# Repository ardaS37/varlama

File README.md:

# Varlama — Card and Phone Attendance System

Varlama is an experimental attendance system designed for boarding houses, dormitories, hostels, and other managed facilities. It combines an ESP32 reader with an optional Android phone-card application so that authorized residents can record attendance without sharing personal identity data with the reader.

## Part 1 — ESP32 card reader and attendance panel

The ESP32 firmware reads RFID/MIFARE cards through an RC522 module, stores authorized credentials and attendance records on an SD card, and shows the latest result on an I2C LCD. A local web panel is served by the device for registering cards, managing residents, configuring Wi-Fi, and exporting attendance data as CSV.

The firmware can also operate as a Wi-Fi access point when an external network is unavailable. Attendance records are designed around a daily check-in model, preventing duplicate entries for the same person on the same day.

### Main hardware

- ESP32 development board
- RC522 RFID reader
- SD card module
- I2C LCD
- Optional Android phone with NFC host-card emulation

The pin mapping and PlatformIO dependencies are documented in `platformio.ini` and the source comments. Before deployment, set a strong local access-point password in `src/main.cpp` and configure the device through the web panel.

## Part 2 — Android phone-card application

The `android-phone-card/` module turns an NFC-capable Android phone into a reusable attendance card. The app stores a provisioned credential locally and exposes it through Android Host Card Emulation (HCE). An administrator can open the phone-provisioning mode on the ESP32, write a one-time credential to the phone, and then use the phone at the reader like a physical card.

The phone app is intentionally small: it provides a provisioning screen, secure local storage for the assigned credential, and an HCE service that responds only to the Yoklama application protocol. It does not contain a server account or a hard-coded student list.

### Android setup

1. Open `android-phone-card/` in Android Studio.
2. Copy `master-key.properties.example` to `master-key.properties` only for local signing configuration.
3. Build and install the debug APK on an NFC-capable Android device.
4. Arm provisioning from the app, then use the ESP32 web panel to assign the phone.

Build output and signing files are intentionally ignored and are not part of this repository.

## Data and privacy notes

Use institution-specific identifiers instead of national ID numbers. Keep the ESP32 panel on a trusted local network, change all default credentials, and protect exported CSV files. This project is a prototype and has not been audited for production security or attendance-law compliance.

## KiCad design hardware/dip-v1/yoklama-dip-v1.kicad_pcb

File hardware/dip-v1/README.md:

# Yoklama — doğrudan lehimlenen modüller için DIP/THT kart, v1

Bu sürüm, hazır ESP32 geliştirme kartı ve modüllerin erkek pinlerini ana PCB'nin deliklerine doğrudan lehimlemek içindir. Ana kart üzerinde SMD montaj yoktur; modüllerin kendi üzerlerindeki SMD parçalar hazır modülün parçasıdır. Soket gerekmez.

**Durum: elektriksel ve PCB kural kontrolleri tamamlanmış prototip tasarım. Fiziksel montaj, USB akım bütçesi ve çalışır cihaz testi yapılmadı.** Gerberlerin bulunması bu testlerin yapıldığı anlamına gelmez.

## Dosyalar

- `yoklama-dip-v1.kicad_pro`: KiCad 10 projesi.
- `yoklama-dip-v1.kicad_sch`: bağlantı şeması; modül ve destek bileşenleri pin adlarıyla gösterilir.
- `yoklama-dip-v1.kicad_pcb`: yolları çizilmiş iki katmanlı PCB.
- `Yoklama.pretty`, `Yoklama.kicad_sym`, `fp-lib-table`, `sym-lib-table`: proje içi kütüphaneler; taşınırken birlikte tutulmalı.
- `BOM.csv`: parça listesi; `pinout.csv`: firmware ile eşleştirilmiş bağlantılar.
- `exports/assembly.svg`: üst yüzün gerçek KiCad montaj/baskı çizimi.
- `exports/board.svg`: iki bakır katman ve üst baskı.
- `exports/yoklama-dip-v1.svg`: şema önizlemesi.
- `gerbers/`: 7 Gerber katmanı, PTH ve NPTH delik dosyaları ve Gerber iş dosyası.
- `reports/erc.rpt`, `reports/drc.rpt`: son KiCad kontrolleri.
- `reports/verification.json`: kod, şema ve PCB bağlantılarının karşılaştırması.

## Kart ve besleme

| Özellik | Değer |
|---|---|
| Ana PCB | 152,4 × 127 mm, dikdörtgen |
| Katman | 2 bakır katman |
| Önerilen malzeme | FR-4, 1,6 mm, 1 oz bakır |
| Sinyal yolları | 0,30 mm |
| Güç/toprak yolları | 0,80 mm, iki yüzde GND dolgu |
| Minimum açıklık | 0,25 mm |
| Modül pin delikleri | 1,00 mm bitmiş PTH; 1,80 mm pad |
| Modül pin adımı | 2,54 mm |
| ESP32 sıra aralığı | 25,40 mm, 2 × 19 pin |
| Montaj delikleri | 4 × 3,20 mm NPTH, M3 |
| Besleme | Yalnızca ESP32 geliştirme kartının USB girişi |

USB'den gelen 5 V, geliştirme kartının 5V pininden SD modülüne, LCD'ye ve buzzer devresine dağıtılır. RC522 ve I²C'nin ESP tarafı geliştirme kartının 3V3 çıkışını kullanır. Ana kartta ayrı adaptör girişi yoktur. USB kaynağının ve geliştirme kartının 5 V yolunun toplam yüke uygunluğu ilk cihazda ölçülmelidir; bilgisayar USB portundan sınırsız akım varsayılmadı.

## Modül yerleşimi ve yön

Tüm yönler **üstten, modüllerin takıldığı yüzden görünüş** içindir. Alt yüz bakırını elle aynalamayın; üretim dosyaları doğru katman yönleriyle dışa aktarıldı.

- **U1:** ESP32-DevKitC V4 / WROOM, 38 pin, anten üstte ve USB aşağıda. Solda üst pin 3V3, sol alt pin 5V; sağ üst pin GND. `SD0/1/2/3`, `CMD`, `CLK` gibi flash pinleri bağlanmadı. WROVER, S3 veya 30 pinli kart için uygun değildir.
- **J1:** 8 pinli RC522, soldan sağa `SDA/SS, SCK, MOSI, MISO, IRQ, GND, RST, 3V3`. IRQ boş bırakıldı. Modül gövdesi pin sırasının üstüne doğru uzanır. Yer ayrılan zarf yaklaşık 40 × 60 mm; modül montaj delikleri için tahminle delik açılmadı.
- **J2:** Kullanıcının fotoğrafındaki 42 × 24 mm, regülatör ve seviye tamponu taşıyan microSD modülü. Üstten alta `GND, VCC, MISO, MOSI, SCK, CS`; gövde pinlerin sağına uzanır. VCC=5 V. Bu bağlantı çıplak microSD soketi veya regülatörsüz 3,3 V kart için değildir.
- **J3:** Klasik PCF8574 I²C LCD, soldan sağa `GND, VCC, SDA, SCL`. 4 pin doğrudan lehim bağlantısıdır. LCD kenarda dik montaj için düşünülmüştür; mevcut açılı pinleri hizalanmalıdır. LCD'nin ekran gövdesi, vida aralıkları ve kutusu bu revizyonda ölçülendirilmedi; 4 pin bağlantısı LCD için tek başına mekanik taşıyıcı sayılmamalıdır.

Üretimden önce `assembly.svg` gerçek boyutta (%100, sayfaya sığdır kapalı) basılıp modüllerin pinleriyle karşılaştırılmalıdır. Kullanıcının kabul ettiği standart ESP32 ayak izi esas alındı; fiziksel kart ölçülmedi. Sağ açılı pinleri olan modüller için pin yönü fiziksel montaj sırasında dikkate alınmalıdır.

ESP32 ve RC522 antenlerinin altında her iki bakır katmanda yol, via, pad ve dolgu yasak alanları bulunur. Bu bölgelere metal bağlantı elemanı eklenmemelidir.

## Firmware bağlantıları

| Modül | Sinyal | GPIO |
|---|---|---:|
| RC522 | SDA/SS | 5 |
| RC522 | SCK | 18 |
| RC522 | MISO | 19 |
| RC522 | MOSI | 23 |
| RC522 | RST | 27 |
| SD | CS | 33 |
| SD | SCK | 14 |
| SD | MISO | 25 |
| SD | MOSI | 26 |
| LCD | SDA, 3,3 V tarafı | 21 |
| LCD | SCL, 3,3 V tarafı | 22 |
| Hazır LED | Direnç üzerinden | 4 |
| Başarılı işlem LED | Direnç üzerinden | 16 |
| Hata LED | Direnç üzerinden | 17 |
| Ağ LED | Direnç üzerinden | 13 |
| Buzzer | Sürücü üzerinden | 32 |

Kod değiştirilmedi. `src/main.cpp` içindeki sabitler esas alındı. RC522 için `SPI.begin()` / `esp32dev` varsayılan VSPI pinleri kullanılır. SD ayrı HSPI pinlerindedir. Eski kök README'deki SD pinlerini kullanmayın. Firmware LCD'yi `16×2`, I²C adresini `0x3F` olarak başlatır; `0x27` adresli bir LCD'de adresi değiştirmek gerekir.

## Destek parçaları ve polarite

- R1–R4: 1 kΩ, 1/4 W; D1–D4: 5 mm LED, 2,54 mm bacak aralığı. LED pad 1=K/katot, pad 2=A/anot. Kare pad katottur. Mavi LED'in parlaklığı ileri gerilimine bağlı olarak düşük olabilir.
- Q1, Q2: **2N7000**, TO-92; pad 1=source, 2=gate, 3=drain. Bacaklar 2,54 mm aralığa açılır. Gate 3V3'e, source ESP32 tarafına, drain LCD'nin 5 V tarafına bağlıdır. R5–R8=4,7 kΩ çekme dirençleri. LCD sırt kartındaki çekme dirençleri 5 V tarafında kalır. Bu dönüştürücü prototipte 100 kHz I²C ile test edilmelidir.
- Q3: **BC337-40**, TO-92; pad 1=collector, 2=base, 3=emitter. R9=1 kΩ, R10=100 kΩ.
- BZ1: **pasif piezo**, 5 V, en fazla 12 mm gövde, 7,62 mm bacak aralığı, en fazla 20 mA. Pad 1 pozitif. Aktif buzzerla firmware'in farklı frekanslı `tone()` sesleri elde edilmez. R11=10 kΩ deşarj direnci; D5=1N4148, pad 1 katot/bant, pad 2 anot.
- C1=100 µF/10 V, C4=10 µF/10 V; 2,54 mm bacak aralığı ve en fazla 5 mm gövde. Kare pad 1 pozitif, pad 2 GND. C2/C3/C5=100 nF seramik, 2,54 mm bacak aralığı, polaritesiz.
- R12/R13=10 kΩ; RC522 ve SD seçme hatlarını açılışta 3V3'e çeker.

Destek parçaları için belirtilen kılıf, bacak sırası ve gövde ölçüsü BOM'un parçasıdır; aynı isimli farklı üretici/kılıf otomatik olarak eşdeğer kabul edilmemelidir.

## Kontrol kapsamı

KiCad ERC, bakır aralıkları, bağlantısız padler ve şema-PCB eşleşmesi kontrol edildi. GPIO eşlemesi ayrıca mevcut firmware sabitleriyle karşılaştırıldı. RF performansı, SPI sinyal bütünlüğü, SD yazma sırasında besleme düşümü, LCD'nin gerçek adresi ve mekanik montaj ancak ilk fiziksel prototiple doğrulanabilir. Bu revizyon için üretim siparişi verilmedi.

## Yeniden üretme

KiCad 10 ile gelen Python'da `pcbnew` ve `numpy` kullanılır. `build_design.py` PCB'yi sıfırdan oluşturur ve elle yapılan değişiklikleri üzerine yazar; elle düzenlemeden önce kopya alın.

1. `build_design.py` çalıştırılır.
2. KiCad CLI ile şema netlisti `reports/schematic.net` dosyasına aktarılır.
3. `route_board.py`, sonra `finish_board.py` çalıştırılır.
4. KiCad CLI `pcb drc --refill-zones --save-board --schematic-parity` ve `sch erc` çalıştırılır.
5. `verify_design.py` çalıştırılır; dışa aktarımlar son PCB'den yenilenir.

## Referanslar

- [Espressif DevKitC V4 ölçü çizimi](https://dl.espressif.com/dl/schematics/esp32_devkitc_v4_dimensions.pdf)
- [Espressif DevKitC V4 şeması](https://dl.espressif.com/dl/schematics/esp32_devkitc_v4-sch.pdf)
- [Espressif DevKitC pinleri ve besleme seçenekleri](https://docs.espressif.com/projects/esp-idf/en/release-v4.4/esp32/hw-reference/esp32/get-started-devkitc.html)
- [NXP PCF8574 veri sayfası](https://www.nxp.com/docs/en/data-sheet/PCF8574_PCF8574A.pdf)
- [onsemi 2N7000 veri sayfası](https://www.onsemi.com/pdf/datasheet/nds7002a-d.pdf)
- [onsemi BC337 veri sayfası](https://www.onsemi.com/pdf/datasheet/bc337-fsc-d.pdf)
- SD modülü: kullanıcının paylaştığı pin etiketleri ve 42 × 24 mm boyut görseli.

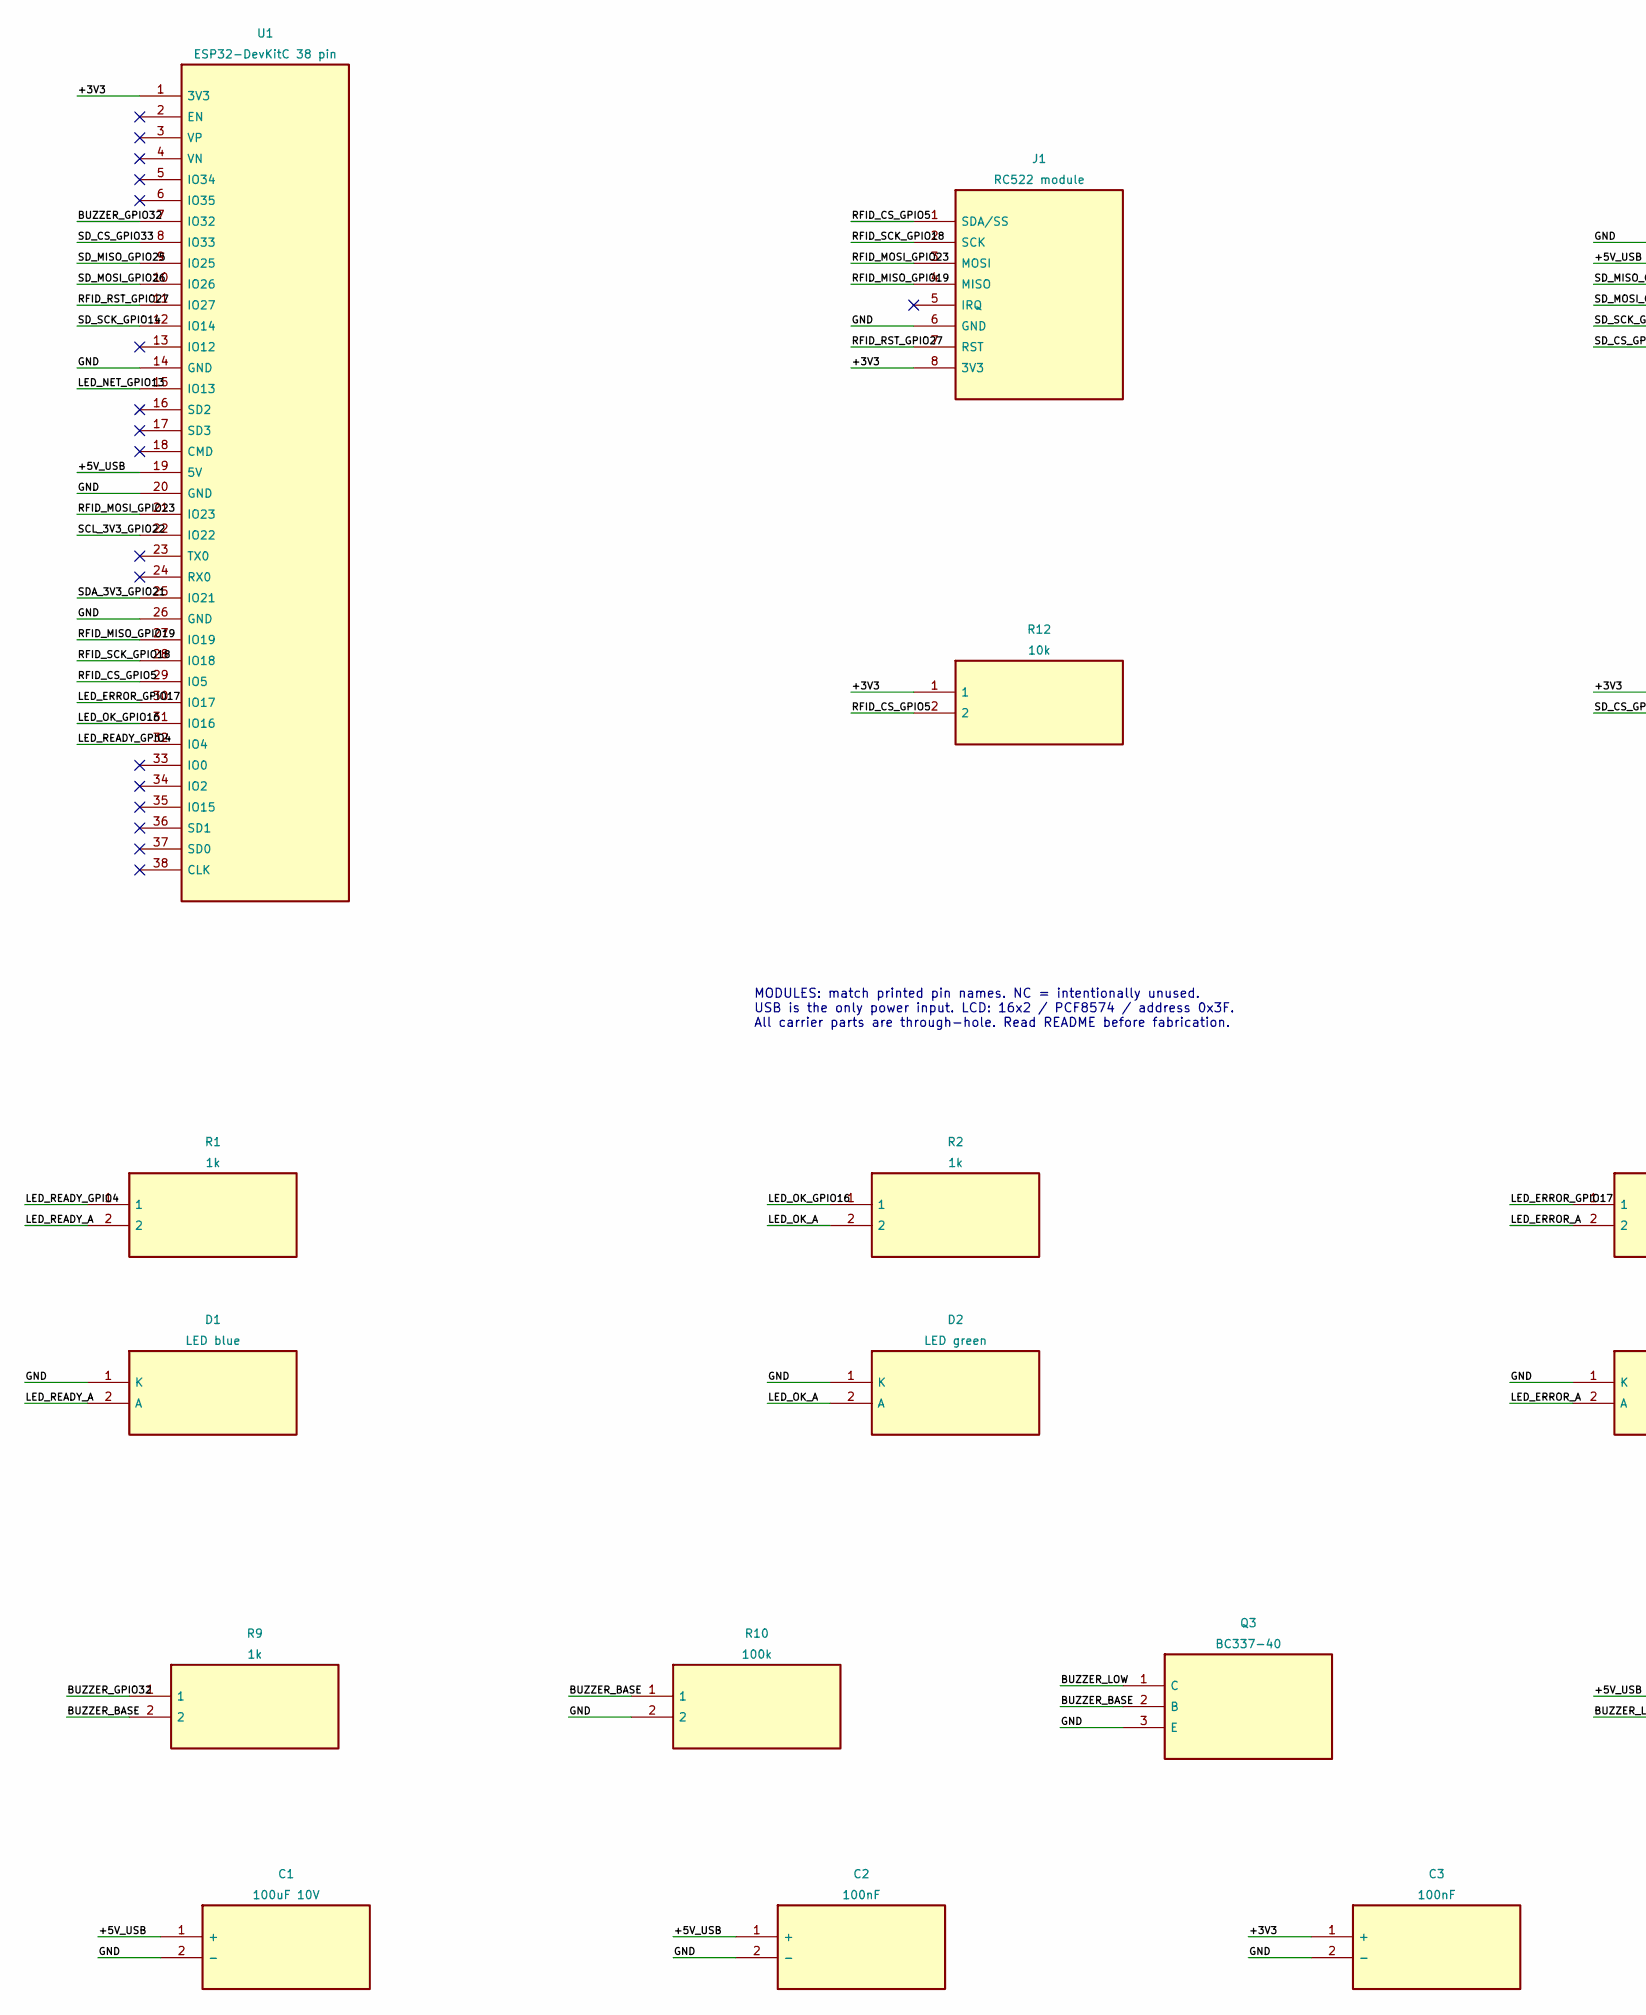
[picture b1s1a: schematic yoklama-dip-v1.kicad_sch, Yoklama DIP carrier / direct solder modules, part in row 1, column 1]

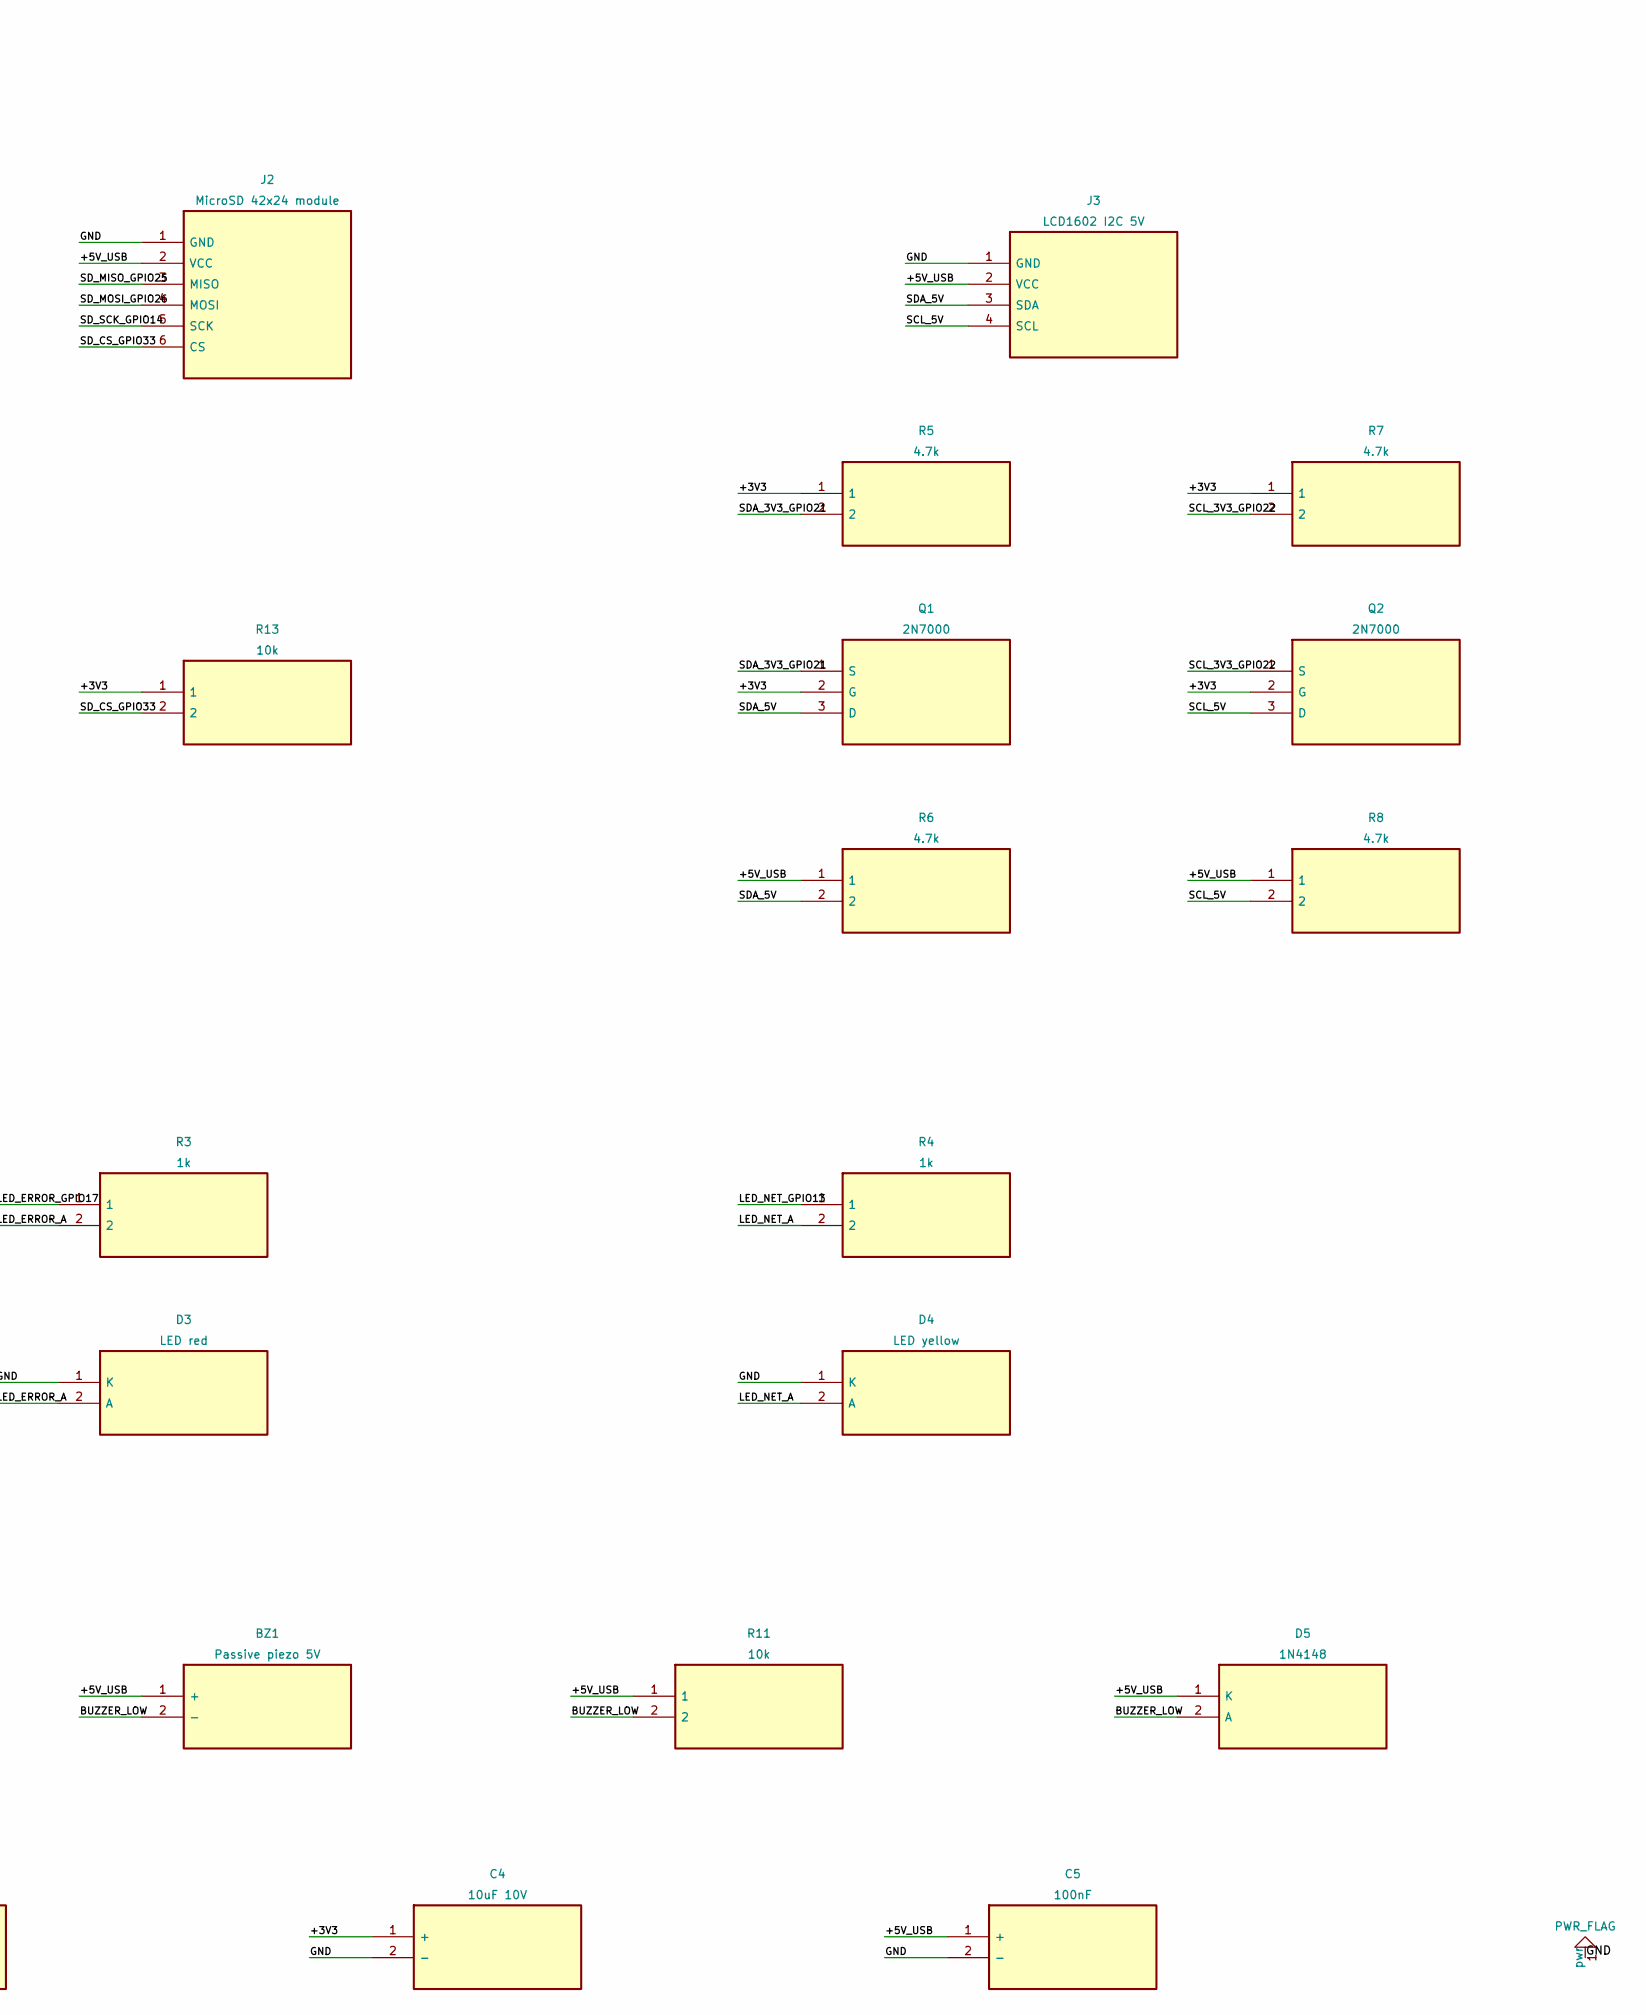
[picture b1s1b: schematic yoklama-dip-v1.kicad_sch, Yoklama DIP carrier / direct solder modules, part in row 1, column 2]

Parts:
BZ1: Passive piezo 5V; BZ1_buzzer
C1: 100uF 10V; C1_cap
C2: 100nF; C2_cap
C3: 100nF; C3_cap
C4: 10uF 10V; C4_cap
C5: 100nF; C5_cap
D1: LED blue; D1_led
D2: LED green; D2_led
D3: LED red; D3_led
D4: LED yellow; D4_led
D5: 1N4148; D5_r
J1: RC522 module; J1_rfid
J2: MicroSD 42x24 module; J2_sd
J3: LCD1602 I2C 5V; J3_header
Q1: 2N7000; Q1_to92
Q2: 2N7000; Q2_to92
Q3: BC337-40; Q3_to92
R1: 1k; R1_r
R2: 1k; R2_r
R3: 1k; R3_r
R4: 1k; R4_r
R5: 4.7k; R5_r
R6: 4.7k; R6_r
R7: 4.7k; R7_r
R8: 4.7k; R8_r
R9: 1k; R9_r
R10: 100k; R10_r
R11: 10k; R11_r
R12: 10k; R12_r
R13: 10k; R13_r
U1: ESP32-DevKitC 38 pin; U1_esp

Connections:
/+3V3: C3.1 (+), C4.1 (+), J1.8 (3V3), Q1.2 (G), Q2.2 (G), R5.1, R7.1, R12.1, R13.1, U1.1 (3V3)
/+5V_USB: BZ1.1 (+), C1.1 (+), C2.1 (+), C5.1 (+), D5.1 (K), J2.2 (VCC), J3.2 (VCC), R6.1, R8.1, R11.1, U1.19 (5V)
/BUZZER_BASE: Q3.2 (B), R9.2, R10.1
/BUZZER_GPIO32: R9.1, U1.7 (IO32)
/BUZZER_LOW: BZ1.2 (-), D5.2 (A), Q3.1 (C), R11.2
/GND: C1.2 (-), C2.2 (-), C3.2 (-), C4.2 (-), C5.2 (-), D1.1 (K), D2.1 (K), D3.1 (K), D4.1 (K), J1.6 (GND), J2.1 (GND), J3.1 (GND), Q3.3 (E), R10.2, U1.14 (GND), U1.20 (GND), U1.26 (GND)
/LED_ERROR_A: D3.2 (A), R3.2
/LED_ERROR_GPIO17: R3.1, U1.30 (IO17)
/LED_NET_A: D4.2 (A), R4.2
/LED_NET_GPIO13: R4.1, U1.15 (IO13)
/LED_OK_A: D2.2 (A), R2.2
/LED_OK_GPIO16: R2.1, U1.31 (IO16)
/LED_READY_A: D1.2 (A), R1.2
/LED_READY_GPIO4: R1.1, U1.32 (IO4)
/RFID_CS_GPIO5: J1.1 (SDA/SS), R12.2, U1.29 (IO5)
/RFID_MISO_GPIO19: J1.4 (MISO), U1.27 (IO19)
/RFID_MOSI_GPIO23: J1.3 (MOSI), U1.21 (IO23)
/RFID_RST_GPIO27: J1.7 (RST), U1.11 (IO27)
/RFID_SCK_GPIO18: J1.2 (SCK), U1.28 (IO18)
/SCL_3V3_GPIO22: Q2.1 (S), R7.2, U1.22 (IO22)
/SCL_5V: J3.4 (SCL), Q2.3 (D), R8.2
/SDA_3V3_GPIO21: Q1.1 (S), R5.2, U1.25 (IO21)
/SDA_5V: J3.3 (SDA), Q1.3 (D), R6.2
/SD_CS_GPIO33: J2.6 (CS), R13.2, U1.8 (IO33)
/SD_MISO_GPIO25: J2.3 (MISO), U1.9 (IO25)
/SD_MOSI_GPIO26: J2.4 (MOSI), U1.10 (IO26)
/SD_SCK_GPIO14: J2.5 (SCK), U1.12 (IO14)

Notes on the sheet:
MODULES: match printed pin names. NC = intentionally unused. USB is the only power input. LCD: 16x2 / PCF8574 / address 0x3F. All carrier parts are through-hole. Read README before fabrication.

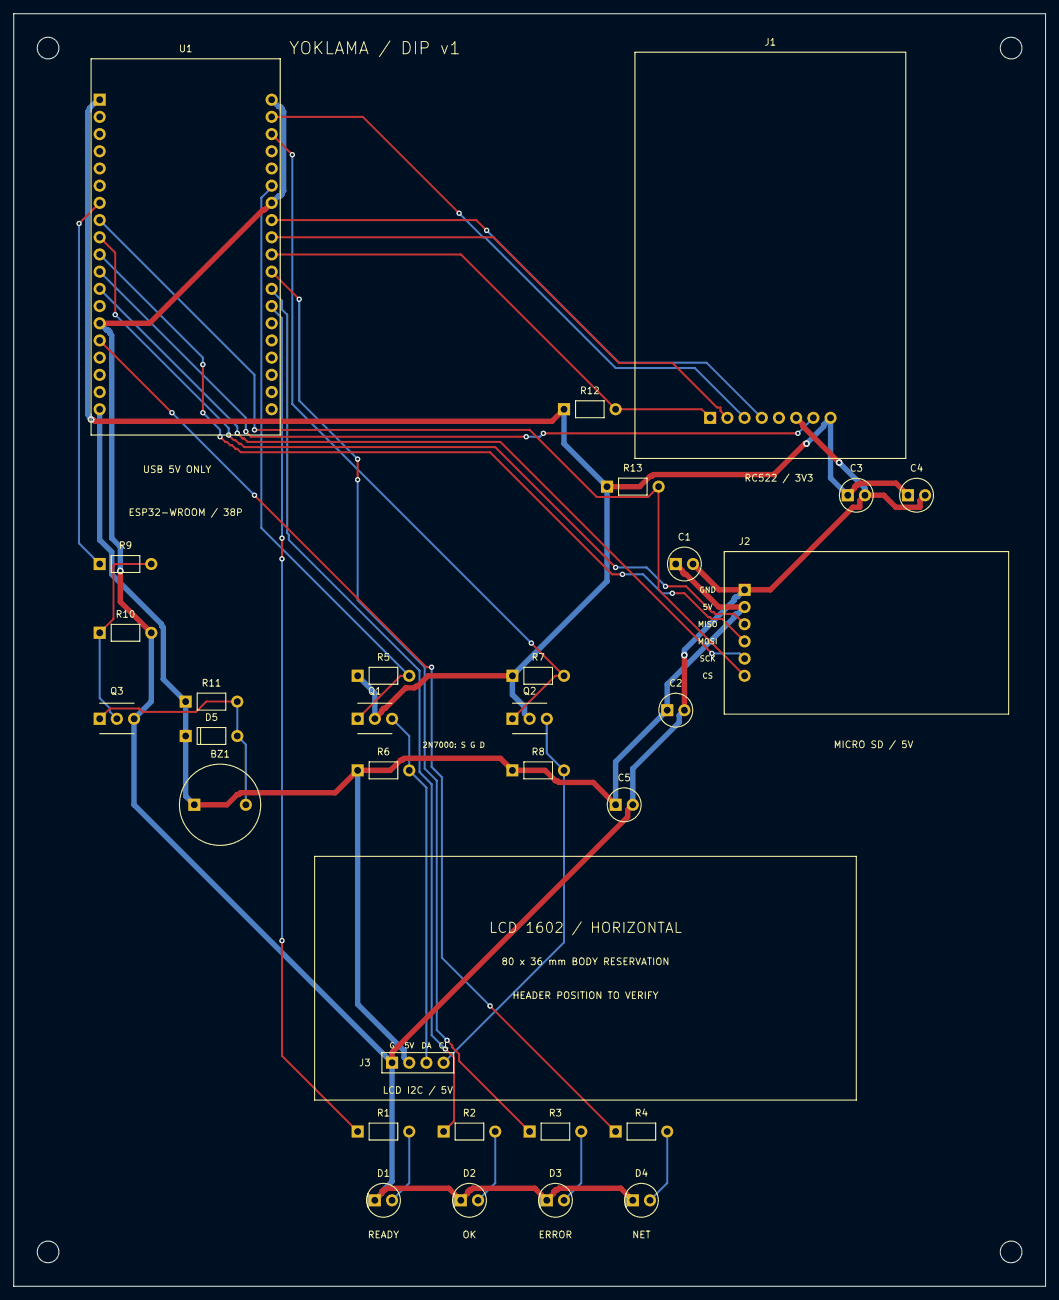
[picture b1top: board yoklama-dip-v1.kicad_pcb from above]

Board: 2 copper layers, 152.4 x 188.0 mm, 35 parts (0 on the bottom side), 27 nets.

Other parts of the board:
H1, H2, H3, H4: M3

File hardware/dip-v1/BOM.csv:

Reference,Value,Footprint,Notes
U1,ESP32-DevKitC 38 pin,Yoklama:U1_esp,"WROOM, 2x19, 25.40 mm row spacing; USB supply only"
J1,RC522 module,Yoklama:J1_rfid,
J2,MicroSD 42x24 module,Yoklama:J2_sd,
J3,LCD1602 I2C 5V,Yoklama:J3_header,
R1,1k,Yoklama:R1_r,"Axial 1/4 W, lead pitch 7.62 mm"
D1,LED blue,Yoklama:D1_led,"5 mm LED, 2.54 mm lead pitch"
R2,1k,Yoklama:R2_r,"Axial 1/4 W, lead pitch 7.62 mm"
D2,LED green,Yoklama:D2_led,"5 mm LED, 2.54 mm lead pitch"
R3,1k,Yoklama:R3_r,"Axial 1/4 W, lead pitch 7.62 mm"
D3,LED red,Yoklama:D3_led,"5 mm LED, 2.54 mm lead pitch"
R4,1k,Yoklama:R4_r,"Axial 1/4 W, lead pitch 7.62 mm"
D4,LED yellow,Yoklama:D4_led,"5 mm LED, 2.54 mm lead pitch"
Q1,2N7000,Yoklama:Q1_to92,"onsemi 2N7000, TO-92, spread leads to 2.54 mm pitch"
R5,4.7k,Yoklama:R5_r,"Axial 1/4 W, lead pitch 7.62 mm"
R6,4.7k,Yoklama:R6_r,"Axial 1/4 W, lead pitch 7.62 mm"
Q2,2N7000,Yoklama:Q2_to92,"onsemi 2N7000, TO-92, spread leads to 2.54 mm pitch"
R7,4.7k,Yoklama:R7_r,"Axial 1/4 W, lead pitch 7.62 mm"
R8,4.7k,Yoklama:R8_r,"Axial 1/4 W, lead pitch 7.62 mm"
R9,1k,Yoklama:R9_r,"Axial 1/4 W, lead pitch 7.62 mm"
R10,100k,Yoklama:R10_r,"Axial 1/4 W, lead pitch 7.62 mm"
Q3,BC337-40,Yoklama:Q3_to92,"TO-92 BC337: 1 collector, 2 base, 3 emitter"
BZ1,Passive piezo 5V,Yoklama:BZ1_buzzer,"Passive piezo, 7.62 mm pitch, <=12 mm body, <=20mA; not an active buzzer"
R11,10k,Yoklama:R11_r,"Axial 1/4 W, lead pitch 7.62 mm"
D5,1N4148,Yoklama:D5_r,"Axial diode, cathode band at pad 1"
C1,100uF 10V,Yoklama:C1_cap,Radial pitch 2.54 mm
C2,100nF,Yoklama:C2_cap,Radial pitch 2.54 mm
C3,100nF,Yoklama:C3_cap,Radial pitch 2.54 mm
C4,10uF 10V,Yoklama:C4_cap,Radial pitch 2.54 mm
C5,100nF,Yoklama:C5_cap,Radial pitch 2.54 mm
R12,10k,Yoklama:R12_r,"Axial 1/4 W, lead pitch 7.62 mm"
R13,10k,Yoklama:R13_r,"Axial 1/4 W, lead pitch 7.62 mm"

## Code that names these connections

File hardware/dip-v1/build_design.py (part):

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        pins.append((side*19+i+1,label,mapping.get(label),side*25.4,i*2.54,typ))
component('U1','ESP32-DevKitC 38 pin',pins,(12.7,12.7),'esp',(46,66),'WROOM, 2x19, 25.40 mm row spacing; USB supply only')
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header('J2','MicroSD 42x24 module',[('GND','GND'),('VCC','+5V_USB'),('MISO','SD_MISO_GPIO25'),('MOSI','SD_MOSI_GPIO26'),('SCK','SD_SCK_GPIO14'),('CS','SD_CS_GPIO33')],(107.95,85.09),(230,43),False,'sd',{'VCC':'power_in','GND':'power_in','MISO':'output','MOSI':'input','SCK':'input','CS':'input'})
header('J3','LCD1602 I2C 5V',[('GND','GND'),('VCC','+5V_USB'),('SDA','SDA_5V'),('SCL','SCL_5V')],(55.88,154.94),(330,43),True,types={'GND':'power_in','VCC':'power_in','SDA':'bidirectional','SCL':'input'})

def resistor(ref,value,n1,n2,xy,sch):
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    resistor('R'+str(4+idx*2),'4.7k','+5V_USB',sig+'_5V',(x,111.76),(schx,116))

# Passive piezo sounder: GPIO -> 1k -> NPN, 100k base pull-down.
resistor('R9','1k','BUZZER_GPIO32','BUZZER_BASE',(12.7,81.28),(45,215))
resistor('R10','100k','BUZZER_BASE','GND',(12.7,91.44),(105,215))
component('Q3','BC337-40',[(1,'C','BUZZER_LOW',0,0,'passive'),(2,'B','BUZZER_BASE',2.54,0,'input'),(3,'E','GND',5.08,0,'passive')],(12.7,104.14),'to92',(165,215),'TO-92 BC337: 1 collector, 2 base, 3 emitter')
component('BZ1','Passive piezo 5V',[(1,'+','+5V_USB',0,0,'passive'),(2,'-','BUZZER_LOW',7.62,0,'passive')],(26.67,116.84),'buzzer',(230,215),'Passive piezo, 7.62 mm pitch, <=12 mm body, <=20mA; not an active buzzer')
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cap('C4','10uF 10V','+3V3','GND',(132.08,71.12),(258,243.84))
cap('C5','100nF','+5V_USB','GND',(88.9,116.84),(328,243.84))
# Pull-ups keep both readers deselected during boot (GPIO5 is also a strap).
resistor('R12','10k','+3V3','RFID_CS_GPIO5',(81.28,58.42),(140,93))
resistor('R13','10k','+3V3','SD_CS_GPIO33',(87.63,69.85),(230,93))

rect(board,0,0,152.4,187.96,p.Edge_Cuts,.05)
for i,(x,y) in enumerate([(5.08,5.08),(147.32,5.08),(5.08,182.88),(147.32,182.88)],1):
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
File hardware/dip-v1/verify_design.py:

from pathlib import Path
import re,json,csv,hashlib
import pcbnew as p
root=Path(__file__).resolve().parent
src=(root.parents[1]/'src/main.cpp').read_text(encoding='utf-8')
b=p.LoadBoard(str(root/'yoklama-dip-v1.kicad_pcb'))
pads={(f.GetReference(),pad.GetNumber()):pad for f in b.GetFootprints() for pad in f.Pads()}
checks=[('RFID_SS',5,'J1','1','RFID_CS_GPIO5'),('RFID_RST',27,'J1','7','RFID_RST_GPIO27'),('SD_CS',33,'J2','6','SD_CS_GPIO33'),('SD_SCK',14,'J2','5','SD_SCK_GPIO14'),('SD_MISO',25,'J2','3','SD_MISO_GPIO25'),('SD_MOSI',26,'J2','4','SD_MOSI_GPIO26'),('LCD_SDA',21,'Q1','1','SDA_3V3_GPIO21'),('LCD_SCL',22,'Q2','1','SCL_3V3_GPIO22'),('LED_READY',4,'R1','1','LED_READY_GPIO4'),('LED_SUCCESS',16,'R2','1','LED_OK_GPIO16'),('LED_ERROR',17,'R3','1','LED_ERROR_GPIO17'),('LED_INTERNET',13,'R4','1','LED_NET_GPIO13'),('BUZZER_PIN',32,'R9','1','BUZZER_GPIO32')]
for const,gpio,ref,pin,net in checks:
    actual=int(re.search(r'constexpr uint8_t '+const+r'\s*=\s*(\d+)',src)[1]);assert actual==gpio,(const,actual,gpio)
    assert pads[(ref,pin)].GetNetname()=='/'+net,(ref,pin)
    assert any(pad.GetNetname()=='/'+net for (r,_),pad in pads.items() if r=='U1'),net
assert 'SPI.begin();' in src
for pin,net in [('2','RFID_SCK_GPIO18'),('3','RFID_MOSI_GPIO23'),('4','RFID_MISO_GPIO19')]:assert pads[('J1',pin)].GetNetname()=='/'+net
assert p.ToMM(pads[('U1','20')].GetPosition().x-pads[('U1','1')].GetPosition().x)==25.4
assert len([k for k in pads if k[0]=='U1'])==38
for pad in pads.values():assert pad.GetAttribute() in (p.PAD_ATTRIB_PTH,p.PAD_ATTRIB_NPTH)
erc=(root/'reports/erc.rpt').read_text();drc=(root/'reports/drc.rpt').read_text()
assert 'Errors 0  Warnings 0' in erc
assert 'Found 0 DRC violations' in drc and 'Found 0 unconnected pads' in drc and 'Found 0 Footprint errors' in drc
report={'firmware_gpio_constants_checked':len(checks),'spi_defaults':'esp32dev VSPI: SCK=18 MISO=19 MOSI=23','esp32_pads':38,'row_spacing_mm':25.4,'all_component_pads_through_hole':True,'erc_errors':0,'erc_warnings':0,'drc_violations':0,'unconnected_pads':0,'schematic_parity_issues':0,'pcb_sha256':hashlib.sha256((root/'yoklama-dip-v1.kicad_pcb').read_bytes()).hexdigest(),'firmware_sha256':hashlib.sha256((root.parents[1]/'src/main.cpp').read_bytes()).hexdigest(),'physical_prototype_tested':False}
(root/'reports/verification.json').write_text(json.dumps(report,indent=2))
with (root/'pinout.csv').open('w',newline='',encoding='utf-8-sig') as f:
    w=csv.writer(f);w.writerow(['Firmware constant','GPIO','Component','Pad','Net']);w.writerows(checks)
    for gpio,pin,net in [(18,2,'RFID_SCK_GPIO18'),(23,3,'RFID_MOSI_GPIO23'),(19,4,'RFID_MISO_GPIO19')]:w.writerow(['VSPI default',gpio,'J1',pin,net])
print(json.dumps(report,indent=2))
